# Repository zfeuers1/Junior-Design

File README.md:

Junior-Design-Project
=============

Project for my Junior Design class at Binghamton University (Spring 2014).

Look at "Project Description.pdf" for more details.

Code is all in RobotControl

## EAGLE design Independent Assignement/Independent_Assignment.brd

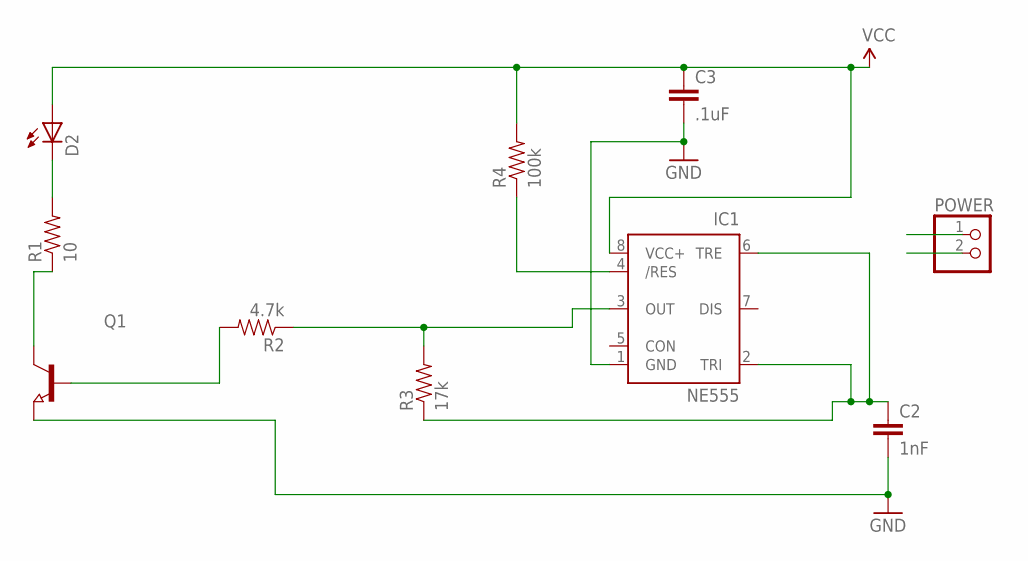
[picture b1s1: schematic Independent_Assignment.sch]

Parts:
C2: 1nF; 0603-CAP
C3: .1uF; 0603-CAP
D2: SFH482
IC1: NE555; DIL-08
POWER: PINHD-1X2; 1X02
Q1: NPN-TRANSISTOR_SOT23W; SOT23W
R1: 10; 0603-RES
R2: 4.7k; 0603-RES
R3: 17k; 0603-RES
R4: 100k; 0603-RES

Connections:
GND: C2.2, C3.2, IC1.1 (GND), POWER.2, Q1.3 (E)
unnamed: C2.1, IC1.2 (TRI), IC1.6 (TRE), R3.1
unnamed: D2.K (C), R1.2
unnamed: Q1.2 (C), R1.1
unnamed: Q1.1 (B), R2.2
unnamed: IC1.3 (OUT), R2.1, R3.2
unnamed: IC1.4 (/RES), R4.1
VCC: C3.1, D2.A, IC1.8 (VCC+), POWER.1, R4.2

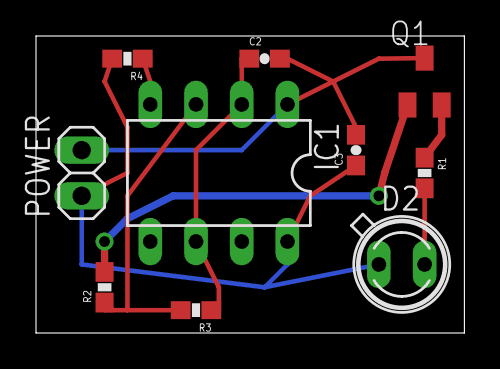
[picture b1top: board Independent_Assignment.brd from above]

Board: 2 copper layers, 23.8 x 16.5 mm, 10 parts (0 on the bottom side), 8 nets.

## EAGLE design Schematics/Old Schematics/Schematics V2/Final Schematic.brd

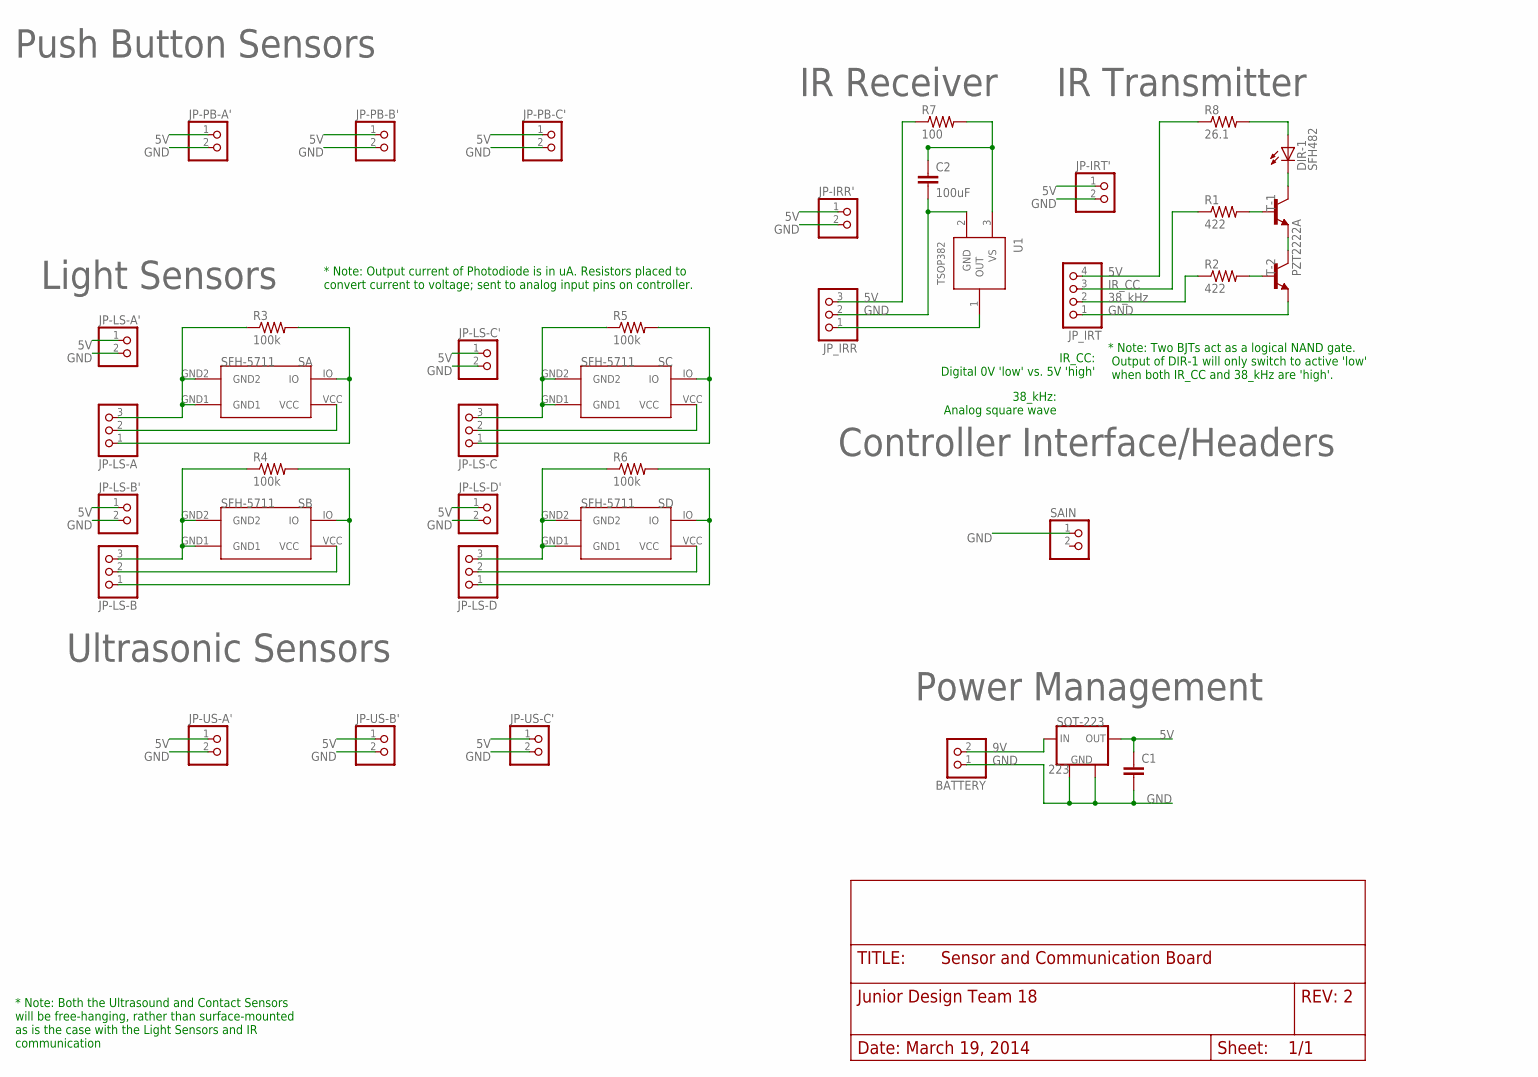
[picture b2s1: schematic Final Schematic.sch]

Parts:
BATTERY: PINHD-1X2; 1X02
C1: CAP0603-CAP; 0603-CAP
C2: 100uF; 1206
DIR-1: SFH482
JP-IRR': PINHD-1X2; 1X02
JP-IRT': PINHD-1X2; 1X02
JP-LS-A: PINHD-1X3; 1X03
JP-LS-A': PINHD-1X2; 1X02
JP-LS-B: PINHD-1X3; 1X03
JP-LS-B': PINHD-1X2; 1X02
JP-LS-C: PINHD-1X3; 1X03
JP-LS-C': PINHD-1X2; 1X02
JP-LS-D: PINHD-1X3; 1X03
JP-LS-D': PINHD-1X2; 1X02
JP-PB-A': PINHD-1X2; 1X02
JP-PB-B': PINHD-1X2; 1X02
JP-PB-C': PINHD-1X2; 1X02
JP-US-A': PINHD-1X2; 1X02
JP-US-B': PINHD-1X2; 1X02
JP-US-C': PINHD-1X2; 1X02
JP_IRR: PINHD-1X3; 1X03
JP_IRT: PINHD-1X4; 1X04
R1, R2: 422; R2512
R3, R4, R5, R6: 100k; 0805
R7: 100; 0805
R8: 26.1; R2512
SAIN: PINHD-1X2; 1X02
SFH-5711-A, SFH-5711-B, SFH-5711-C, SFH-5711-D: 5711; DIODE
SOT-223: 223; SOT223
T-1, T-2: PZT2222A; SOT223
U1: TSOP382

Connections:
5V: C1.1, JP-IRR'.1, JP-IRT'.1, JP-LS-A'.1, JP-LS-B'.1, JP-LS-C'.1, JP-LS-D'.1, JP-PB-A'.1, JP-PB-B'.1, JP-PB-C'.1, JP-US-A'.1, JP-US-B'.1, JP-US-C'.1, SOT-223.GND1 (OUT)
9V-BAT: BATTERY.2, SOT-223.OUT (IN)
GND: BATTERY.1, C1.2, JP-IRR'.2, JP-IRT'.2, JP-LS-A'.2, JP-LS-B'.2, JP-LS-C'.2, JP-LS-D'.2, JP-PB-A'.2, JP-PB-B'.2, JP-PB-C'.2, JP-US-A'.2, JP-US-B'.2, JP-US-C'.2, SAIN.1, SOT-223.GND2 (GND1), SOT-223.IN (GND2)
GND-IR-R: C2.2, JP_IRR.2, U1.2 (GND)
GND-IR-T: JP_IRT.1, T-2.3 (E)
GND-LS-A: JP-LS-A.3, R3.1, SFH-5711-A.GND1, SFH-5711-A.GND2
GND-LS-B: JP-LS-B.3, R4.1, SFH-5711-B.GND1, SFH-5711-B.GND2
GND-LS-C: JP-LS-C.3, R5.1, SFH-5711-C.GND1, SFH-5711-C.GND2
GND-LS-D: JP-LS-D.3, R6.1, SFH-5711-D.GND1, SFH-5711-D.GND2
IO-LS-A: JP-LS-A.1, R3.2, SFH-5711-A.IO
IO-LS-B: JP-LS-B.1, R4.2, SFH-5711-B.IO
IO-LS-C: JP-LS-C.1, R5.2, SFH-5711-C.IO
IO-LS-D: JP-LS-D.1, R6.2, SFH-5711-D.IO
unnamed: DIR-1.A, R8.2
unnamed: DIR-1.K (C), T-1.2 (C), T-1.4 (C)
unnamed: R2.2, T-2.1 (B)
unnamed: R1.2, T-1.1 (B)
unnamed: T-1.3 (E), T-2.2 (C), T-2.4 (C)
VCC-IR-R: JP_IRR.3, R7.1
VCC-IR-T: JP_IRT.4, R8.1
VCC-LS-A: JP-LS-A.2, SFH-5711-A.VCC
VCC-LS-B: JP-LS-B.2, SFH-5711-B.VCC
VCC-LS-C: JP-LS-C.2, SFH-5711-C.VCC
VCC-LS-D: JP-LS-D.2, SFH-5711-D.VCC
VIN-IR-1: JP_IRT.3, R1.1
VIN-IR-2: JP_IRT.2, R2.1
VOUT-IR-R: JP_IRR.1, U1.1 (OUT)
VS-IR-R: C2.1, R7.2, U1.3 (VS)

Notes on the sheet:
IR Receiver
IR Transmitter
Light Sensors
Controller Interface/Headers
Ultrasonic Sensors
Push Button Sensors
* Note: Both the Ultrasound and Contact Sensors will be free-hanging, rather than surface-mounted as is the case with the Light Sensors and IR communication
SFH-5711
Power Management
GND
IR_CC
38_kHz
* Note: Two BJTs act as a logical NAND gate. Output of DIR-1 will only switch to active 'low' when both IR_CC and 38_kHz are 'high'.
* Note: Output current of Photodiode is in uA. Resistors placed to convert current to voltage; sent to analog input pins on controller.
38_kHz: Analog square wave
IR_CC: Digital 0V 'low' vs. 5V 'high'

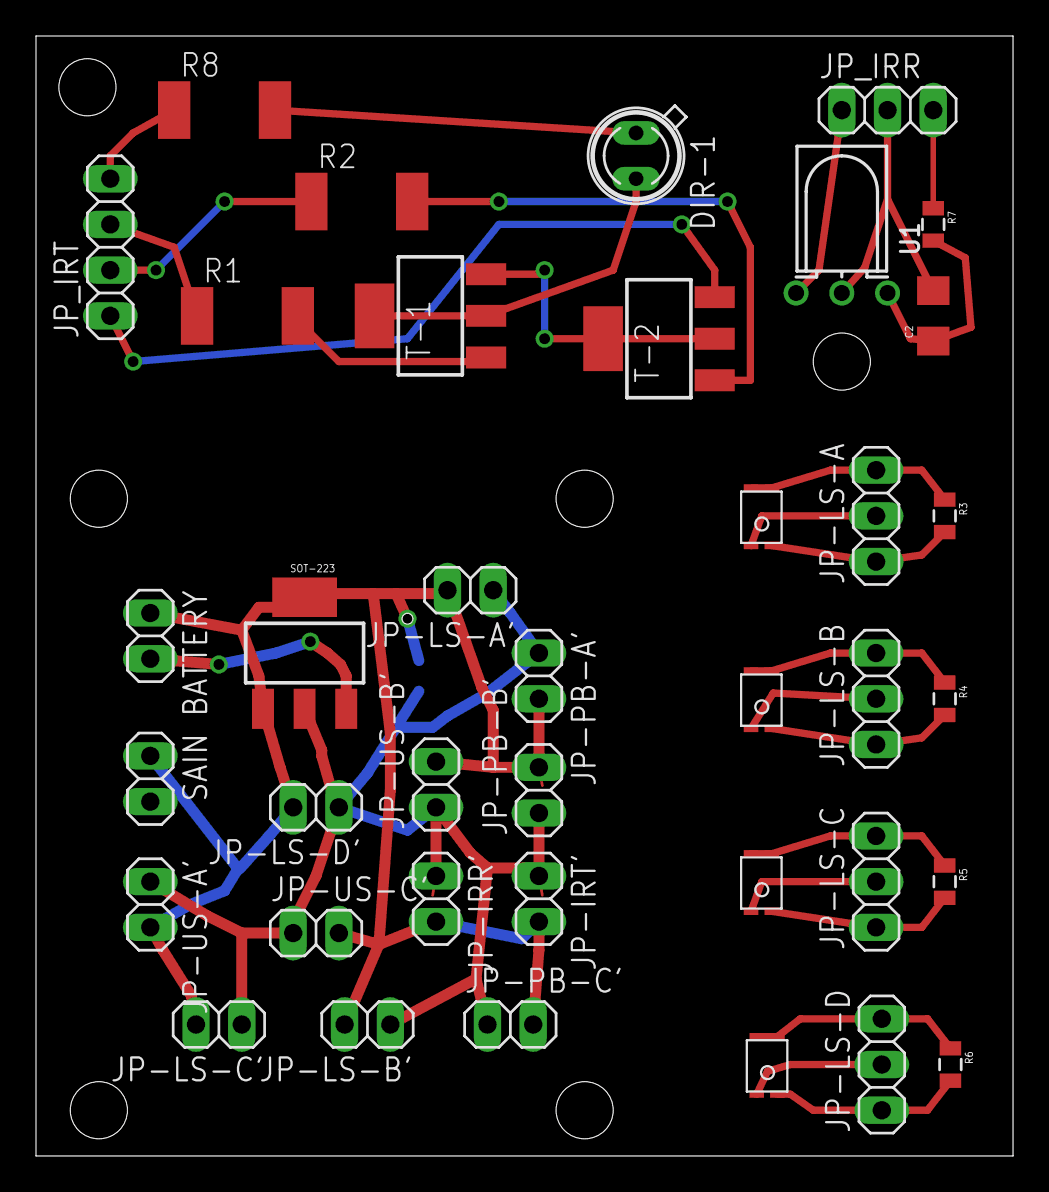
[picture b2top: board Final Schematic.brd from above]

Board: 2 copper layers, 54.3 x 62.2 mm, 39 parts (1 on the bottom side), 28 nets.

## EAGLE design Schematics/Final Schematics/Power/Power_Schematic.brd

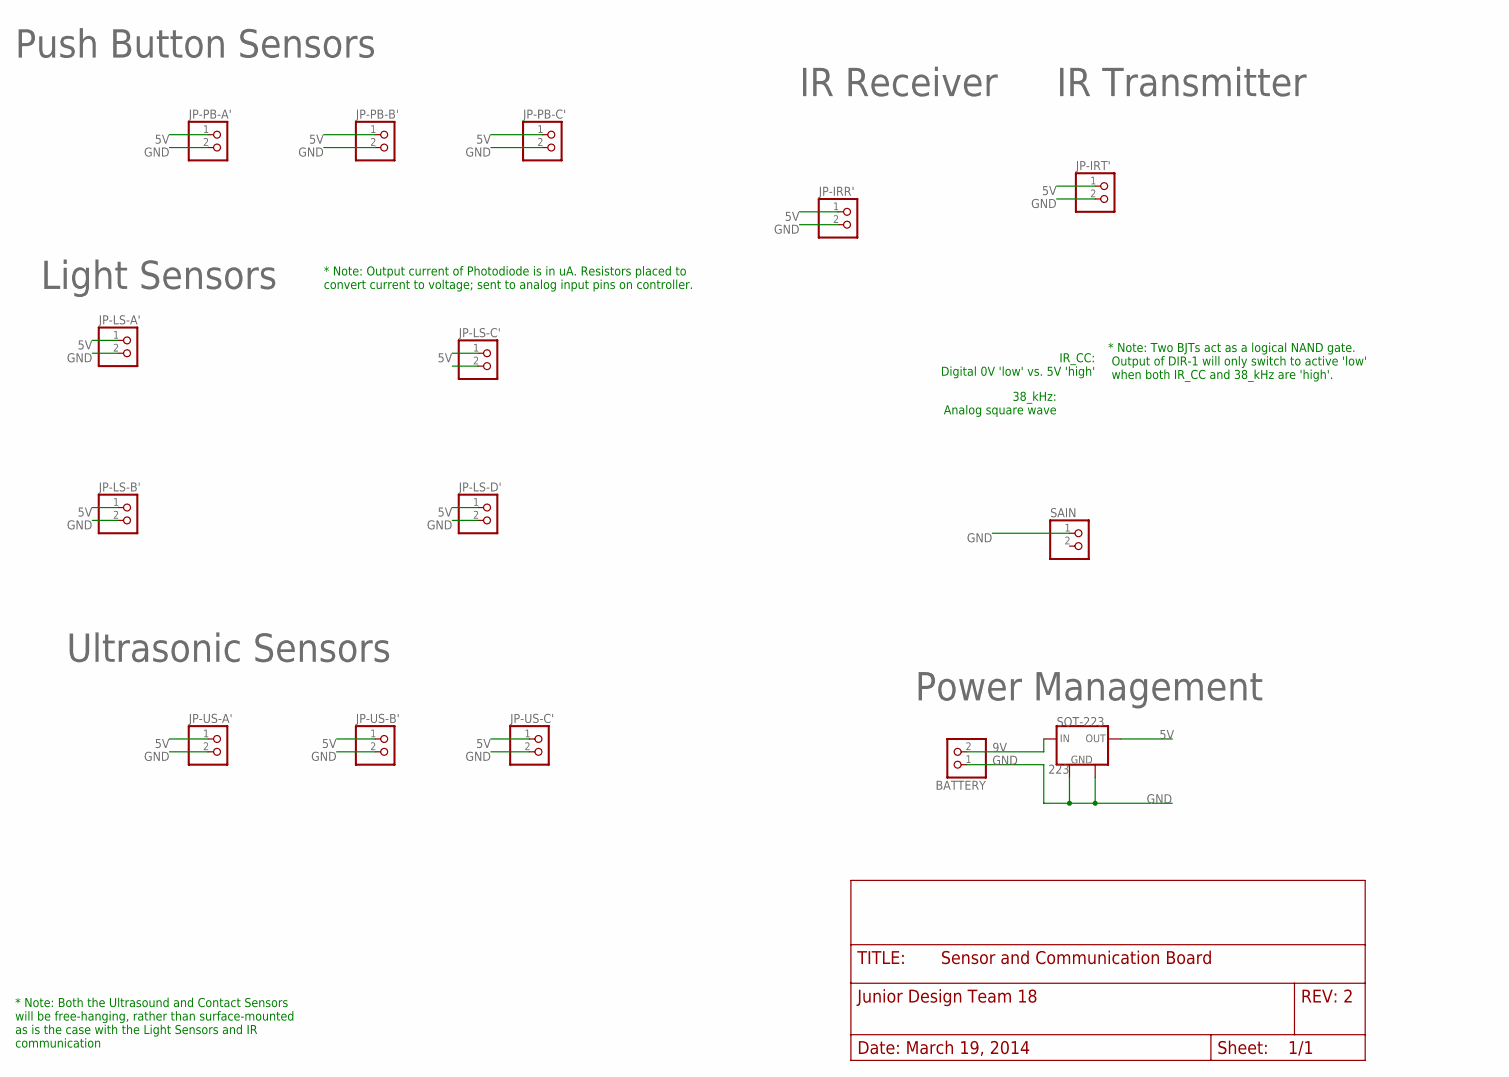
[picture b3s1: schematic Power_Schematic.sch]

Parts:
BATTERY: PINHD-1X2; 1X02
JP-IRR': PINHD-1X2; 1X02
JP-IRT': PINHD-1X2; 1X02
JP-LS-A': PINHD-1X2; 1X02
JP-LS-B': PINHD-1X2; 1X02
JP-LS-C': PINHD-1X2; 1X02
JP-LS-D': PINHD-1X2; 1X02
JP-PB-A': PINHD-1X2; 1X02
JP-PB-B': PINHD-1X2; 1X02
JP-PB-C': PINHD-1X2; 1X02
JP-US-A': PINHD-1X2; 1X02
JP-US-B': PINHD-1X2; 1X02
JP-US-C': PINHD-1X2; 1X02
SAIN: PINHD-1X2; 1X02
SOT-223: 223; SOT223

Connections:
5V: JP-IRR'.1, JP-IRT'.1, JP-LS-A'.1, JP-LS-B'.1, JP-LS-C'.1, JP-LS-D'.1, JP-PB-A'.1, JP-PB-B'.1, JP-PB-C'.1, JP-US-A'.1, JP-US-B'.1, JP-US-C'.1, SOT-223.GND1 (OUT)
9V-BAT: BATTERY.2, SOT-223.OUT (IN)
GND: BATTERY.1, JP-IRR'.2, JP-IRT'.2, JP-LS-A'.2, JP-LS-B'.2, JP-LS-C'.2, JP-LS-D'.2, JP-PB-A'.2, JP-PB-B'.2, JP-PB-C'.2, JP-US-A'.2, JP-US-B'.2, JP-US-C'.2, SAIN.1, SOT-223.GND2 (GND1), SOT-223.IN (GND2)

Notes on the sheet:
IR Receiver
IR Transmitter
Light Sensors
Ultrasonic Sensors
Push Button Sensors
* Note: Both the Ultrasound and Contact Sensors will be free-hanging, rather than surface-mounted as is the case with the Light Sensors and IR communication
Power Management
GND
* Note: Two BJTs act as a logical NAND gate. Output of DIR-1 will only switch to active 'low' when both IR_CC and 38_kHz are 'high'.
* Note: Output current of Photodiode is in uA. Resistors placed to convert current to voltage; sent to analog input pins on controller.
38_kHz: Analog square wave
IR_CC: Digital 0V 'low' vs. 5V 'high'

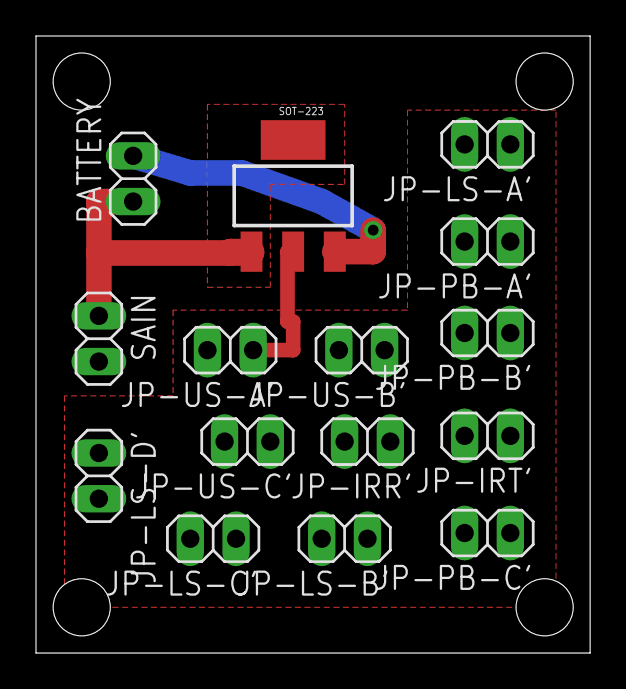
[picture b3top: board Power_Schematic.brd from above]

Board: 2 copper layers, 30.8 x 34.3 mm, 15 parts (0 on the bottom side), 3 nets.

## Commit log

2014-02-26 first upload
2014-02-28 adding block diagram and others
2014-02-28 fix folder v2
2014-02-28 organize into folders
2014-02-28 add project charic.
2014-02-28 add project description
2014-02-28 power management
2014-03-05 button and ultrasonic tester code
2014-03-05 Libray used for ultrasonic sensor
2014-03-06 adding schematics
2014-03-07 added BOM
2014-03-07 added Flowcharts
2014-03-12 added lightSe Sensor Readings
2014-03-12 uncommented useful code
2014-03-19 added genwave and other..
2014-04-17 added new code and ogranized everything
2014-04-17 moved projectDescription.pdf
2014-04-18 started the Light Sensor Algorithm
2014-05-05 added some new libraries and changed main robot control
2014-05-05 finished libraries and added highlighting
2014-05-05 started gameplay algorithm
2014-05-05 added IR library
2014-05-05 commented setup()
2014-05-05 fixed which button to start game
2014-05-07 added some obstacle avoidance
2014-05-07 merge
2014-05-07 edited for testing gameplay
2014-05-08 added final obstacle avoidance algorithm (may need some tweaking. aka not 'final')
2014-05-08 updated the version
2014-05-09 little changes to speed and turn
2014-05-09 changed turn constant
2014-05-12 totally new gameplay algorith...simplified
2014-05-12 took out atObstacle global variable
2014-05-12 added to readButtonpressed
2014-05-12 finished gameplay
2014-05-15 final software
2014-05-16 final code
